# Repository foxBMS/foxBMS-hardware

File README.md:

# foxBMS

foxBMS is a free, open and flexible development environment to design battery
management systems. It is the first modular open source BMS development
platform.

## foxBMS Project Setup
The foxBMS project consists of several repositories.

The foxConda-installer repository contains the installer for the foxConda
environment. This environment provides all the tools necessary to generate the
documentation, compile the code for the MCUs and flash the generated binaries on
the MCUs (e.g., Python, git, GCC).

The starting point to get foxBMS is the foxBMS-setup
repository (https://github.com/foxBMS/foxBMS-setup), which contains
the general setup files for the foxBMS project. It includes a setup script
(bootstrap.py) which clones all the other needed repositories. The needed
documentation will be generated automatically after these repositories have been
cloned. The generated documentation is found in the directory ./build.
After the bootstrap step, the top project directory (foxBMS-setup) structure
looks like this:

 - foxBMS-setup <dir>
  - .git <dir> *
  - build <dir>
  - foxBMS-documentation <dir>
  - foxBMS-hardware <dir>
  - foxBMS-primary <dir>
  - foxBMS-secondary <dir>
  - foxBMS-tools <dir>
  - FreeRTOS <dir>
  - hal <dir>
  - .gitignore <file> *
  - bootstrap.py <file>
  - build.py <file>
  - CHANGELOG.md <file>
  - clean.py <file>
  - LICENSE.md <file>
  - README.md <file>
  - wscript <file>

* Directories and files with starting full stop are hidden in Windows in default
configuration.

There is a help available by running "python bootstrap.py -h".

## foxBMS Repositories

The foxConda-installer and foxBMS-setup repositories have already been described.

foxBMS is made out of two Microcontroller Units (MCU), named primary and
secondary. The C code for the primary MCU is found in the repository
foxBMS-primary (https://github.com/foxBMS/foxBMS-primary). The C code for the
secondary MCU is found in the repository foxBMS-secondary
(https://github.com/foxBMS/foxBMS-secondary). The Doxygen documentation is
generated from these sources into ./build/primary/doxygen/html and
./build/secondary/doxygen/html respectively. The main file is in both cases
index.html.

The layout and schematic files for the foxBMS hardware are found in the
foxBMS-hardware repository (https://github.com/foxBMS/foxBMS-hardware).

The Hardware Abstraction Layer (hal) for foxBMS is found in the hal-repository
(https://github.com/foxBMS/hal.) The real time operating system (FreeRTOS) for
foxBMS is found in the FreeRTOS-repository (https://github.com/foxBMS/FreeRTOS.)

The tools needed for foxBMS are in the foxBMS-tools-repository
(https://github.com/foxBMS/foxBMS-tools.)

The general documentation files for the foxBMS project are found in the
foxBMS-documentation repository
(https://github.com/foxBMS/foxBMS-documentation). The sphinx documentation is
found in foxBMS-documentation/doc/sphinx while the Doxygen documentation
configuration is found in foxBMS-documentation/doc/doxygen. The Doxygen
documentation itself is found in the software sources of the primary and
secondary microcontroller. The general documentation, rendered from the sphinx
sources is found in ./build/sphinx/foxBMS-documentation/doc/sphinx/html. The
main file is index.html

A generated version of the Sphinx documentation can be found at
http://foxbms.readthedocs.io/. It explains the structure of the
foxBMS hardware, how to install the foxConda environment and how to use foxConda
to compile and flash the sources.

## Building the Sources
For building the software, open a shell and type "python build.py -h". All
available build options will be displayed. The top build directory is ./build.

## Cleaning the ./build-Directory
For cleaning instructions open a shell and type "python clean.py -h". All
available cleaning options will be displayed.

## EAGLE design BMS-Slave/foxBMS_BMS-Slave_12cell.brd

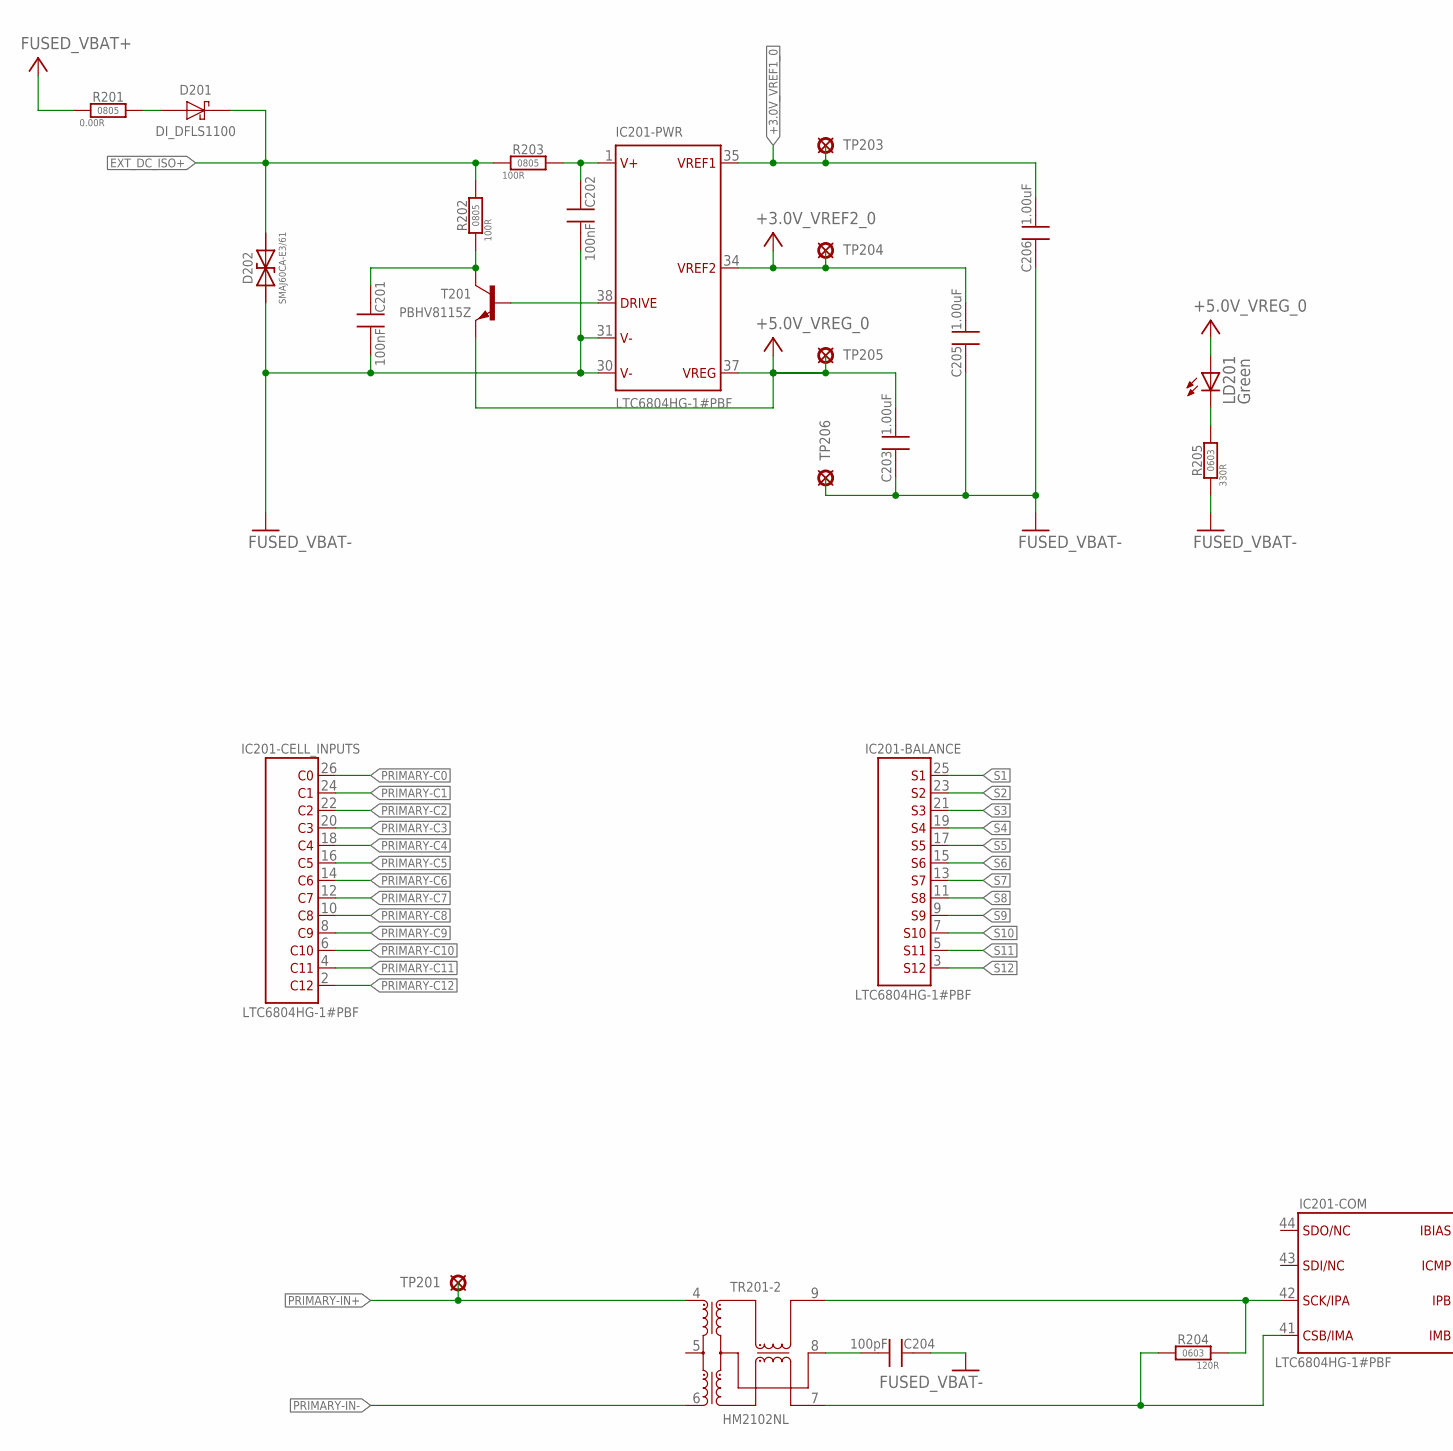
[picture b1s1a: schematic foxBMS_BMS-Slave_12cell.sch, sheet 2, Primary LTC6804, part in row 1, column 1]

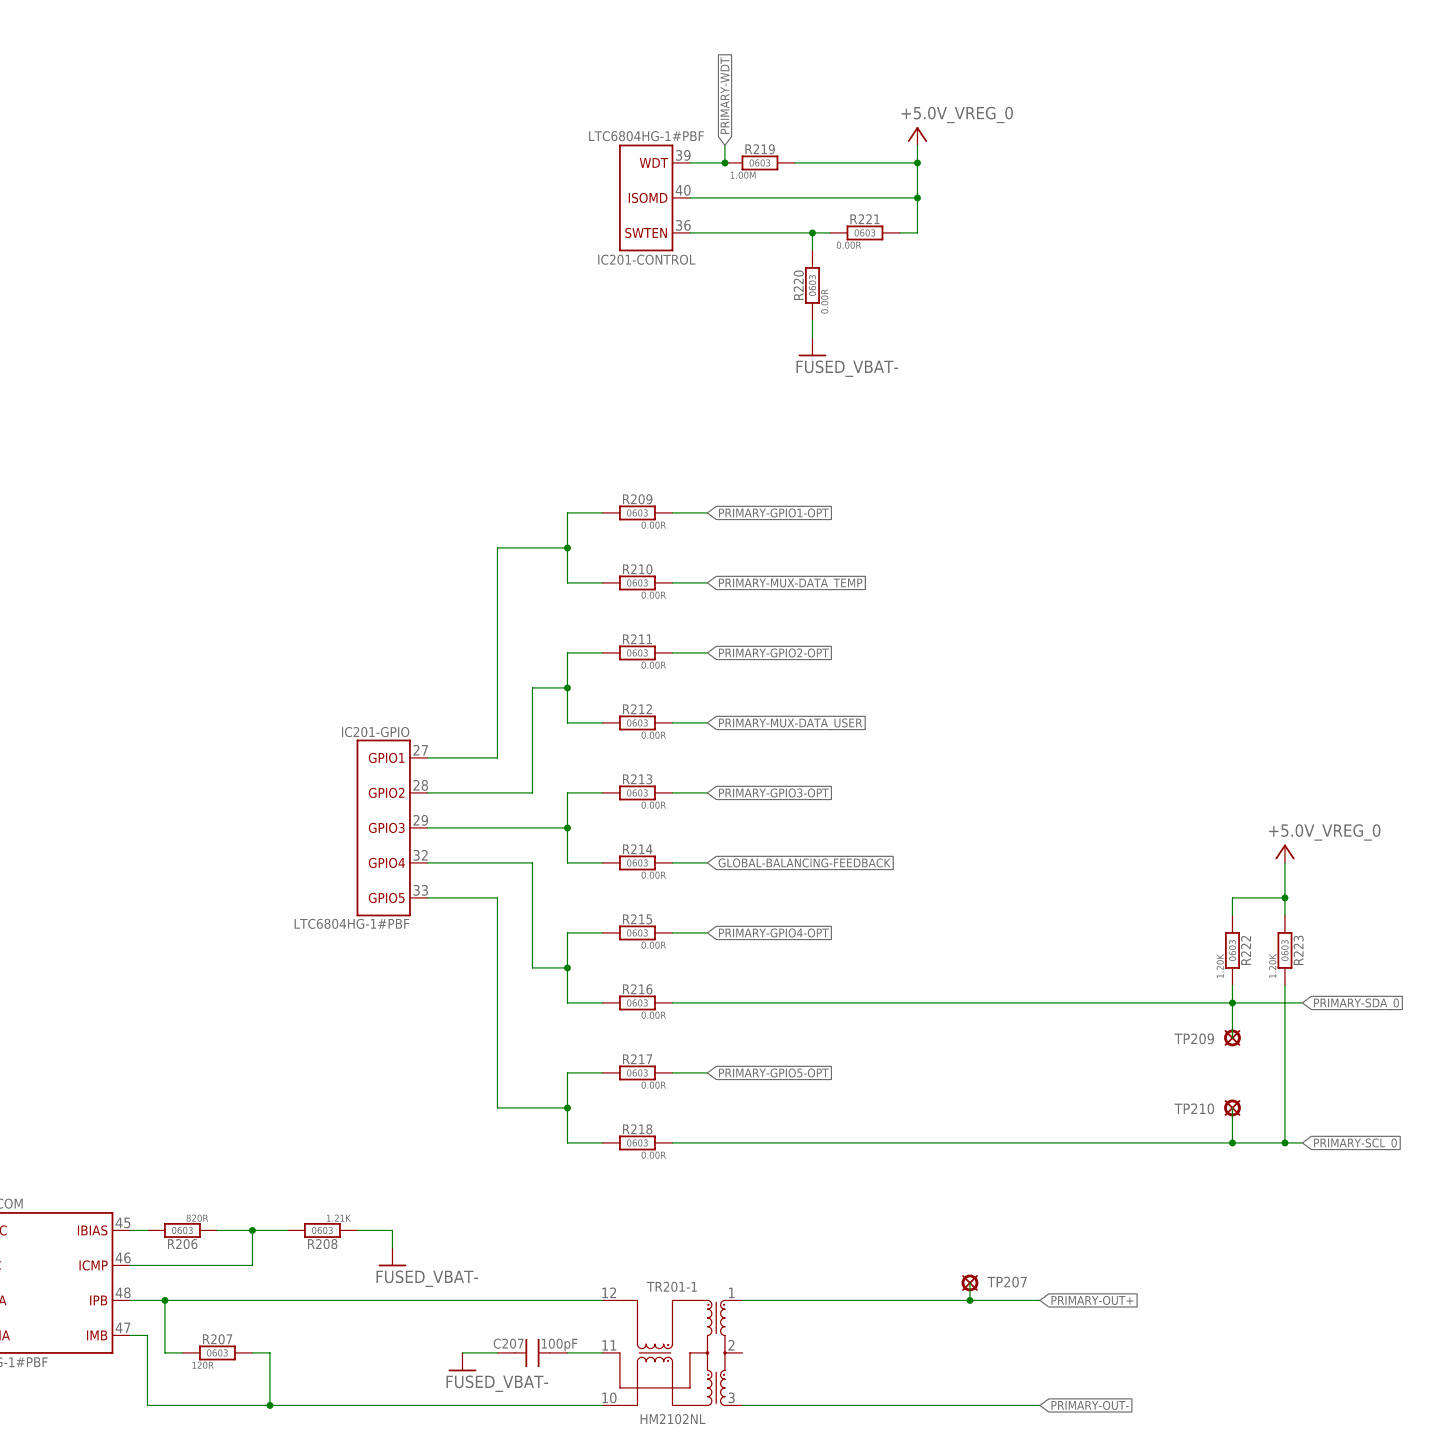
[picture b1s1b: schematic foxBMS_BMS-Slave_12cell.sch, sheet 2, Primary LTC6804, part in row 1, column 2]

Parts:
C201, C202: 100nF, 10%, 100V; C_SMD_0805_(2012)_R_MULTICOMP_REV01
C203, C205, C206: 1uF, 20%, 16V; C_SMD_0603_(1608)_R_KEMET_REV01
C204, C207: 100pF, 15%, 25V; C_SMD_0603_(1608)_R_KEMET_REV01
D201: DI_DFLS1100; POWER_DI_123
D202: SMAJ60CA_VISHAY; D_SMD_SMA_(DO-214AC)_(BIDIR)_R_VISHAY_REV01
IC201: 0_LES_BATTERIE-MANAGEMENT.SMD_LTC6804HG-1; 0_LES_BATTERIE-MANAGEMENT.SMD_IC_SMD_SSOP-48_(G48)_R_LINEAR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
LD201: Green; CHIP-LED0603
R201: 0,00R_0805_R_VISHAY_REV_01; R_SMD_0805_R_VISHAY_REV01
R202, R203: 100R, 1%, 1/10W; R_SMD_0805_R_VISHAY_REV01
R204, R207: 120R, 1%, 1/10W; R_SMD_0603_R_VISHAY_REV01
R205: 330R, 1%, 1/10W; R_SMD_0603_R_VISHAY_REV01
R206: 820R, 1%, 1/10W; R_SMD_0603_R_VISHAY_REV01
R208: 1.21k, 1%, 1/10W; R_SMD_0603_R_VISHAY_REV01
R209, R211, R213, R215, R217, R221: OPT; R_SMD_0603_R_VISHAY_REV01
R210, R212, R214, R216, R218, R220: 0R; R_SMD_0603_R_VISHAY_REV01
R219: 1M, 10%, 1/10W; R_SMD_0603_R_VISHAY_REV01
R222, R223: 1.2k, 10%, 1/10W; R_SMD_0603_R_VISHAY_REV01
T201: PBHV8115Z; D_SMD_SOT223_(SC-73)_R_NXP_REV01
TP201, TP203, TP204, TP205, TP206, TP207, TP209, TP210: CUSTOM_PAD_PAD_2.0X1.5MM; CUSTOM_PAD_PAD2.0X1.5MM
TR201: HM2102NL

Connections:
+3.0V_VREF1_0: C206.2, IC201.35 (VREF1), TP203.P$1
+3.0V_VREF2_0: C205.2, IC201.34 (VREF2), TP204.P$1; also elsewhere on the board
+5.0V_VREG_0: C203.2, IC201.37 (VREG), IC201.40 (ISOMD), LD201.A, R219.2, R221.2, R222.2, R223.2, T201.3 (E), TP205.P$1; also elsewhere on the board
EXT_DC_ISO+: D201.K (C), D202.C (K2), R202.2, R203.1; also elsewhere on the board
FUSED_VBAT+: R201.1; also elsewhere on the board
FUSED_VBAT-: C201.P$2, C202.P$2, C203.1, C204.1, C205.1, C206.1, C207.1, D202.A (K1), IC201.30 (V-1), IC201.31 (V-2), R205.1, R208.1, R220.1, TP206.P$1; also elsewhere on the board
GLOBAL-BALANCING-FEEDBACK: R214.1; also elsewhere on the board
unnamed: C207.2, TR201.11 (CMT)
unnamed: C201.P$1, R202.1, T201.2 (C), T201.4 (C)
unnamed: C204.2, TR201.8 (CMT)
unnamed: IC201.38 (DRIVE), T201.1 (B)
unnamed: IC201.45 (IBIAS), R206.2
unnamed: C202.P$1, IC201.1 (V+), R203.2
unnamed: LD201.C, R205.2
unnamed: D201.A, R201.2
PRIMARY-C0: IC201.26 (C0); also elsewhere on the board
PRIMARY-C1: IC201.24 (C1); also elsewhere on the board
PRIMARY-C2: IC201.22 (C2); also elsewhere on the board
PRIMARY-C3: IC201.20 (C3); also elsewhere on the board
PRIMARY-C4: IC201.18 (C4); also elsewhere on the board
PRIMARY-C5: IC201.16 (C5); also elsewhere on the board
PRIMARY-C6: IC201.14 (C6); also elsewhere on the board
PRIMARY-C7: IC201.12 (C7); also elsewhere on the board
PRIMARY-C8: IC201.10 (C8); also elsewhere on the board
PRIMARY-C9: IC201.8 (C9); also elsewhere on the board
PRIMARY-C10: IC201.6 (C10); also elsewhere on the board
PRIMARY-C11: IC201.4 (C11); also elsewhere on the board
PRIMARY-C12: IC201.2 (C12); also elsewhere on the board
PRIMARY-GPIO0: IC201.27 (GPIO1), R209.2, R210.2
PRIMARY-GPIO1: IC201.28 (GPIO2), R211.2, R212.2
PRIMARY-GPIO1-OPT: R209.1; also elsewhere on the board
PRIMARY-GPIO2-OPT: R211.1; also elsewhere on the board
PRIMARY-GPIO3: IC201.32 (GPIO4), R215.2, R216.2
PRIMARY-GPIO3-OPT: R213.1; also elsewhere on the board
PRIMARY-GPIO4: IC201.33 (GPIO5), R217.2, R218.2
PRIMARY-GPIO4-OPT: R215.1; also elsewhere on the board
PRIMARY-GPIO5: IC201.29 (GPIO3), R213.2, R214.2
PRIMARY-GPIO5-OPT: R217.1; also elsewhere on the board
PRIMARY-ICMP: IC201.46 (ICMP), R206.1, R208.2
PRIMARY-IN+: TP201.P$1, TR201.4 (D+); also elsewhere on the board
PRIMARY-IN-: TR201.6 (D-); also elsewhere on the board
PRIMARY-IN_N1: IC201.41 (CSB/IMA), R204.2, TR201.7 (X-)
PRIMARY-IN_P1: IC201.42 (SCK/IPA), R204.1, TR201.9 (X+)
PRIMARY-MUX-DATA_TEMP: R210.1; also elsewhere on the board
PRIMARY-MUX-DATA_USER: R212.1; also elsewhere on the board
PRIMARY-OUT+: TP207.P$1, TR201.1 (D+); also elsewhere on the board
PRIMARY-OUT-: TR201.3 (D-); also elsewhere on the board
PRIMARY-OUT_N1: IC201.47 (IMB), R207.2, TR201.10 (X-)
PRIMARY-OUT_P1: IC201.48 (IPB), R207.1, TR201.12 (X+)
PRIMARY-SCL_0: R218.1, R223.1, TP210.P$1; also elsewhere on the board
PRIMARY-SDA_0: R216.1, R222.1, TP209.P$1; also elsewhere on the board
PRIMARY-SWTEN: IC201.36 (SWTEN), R220.2, R221.1
PRIMARY-WDT: IC201.39 (WDT), R219.1; also elsewhere on the board
S1: IC201.25 (S1); also elsewhere on the board
S2: IC201.23 (S2); also elsewhere on the board
S3: IC201.21 (S3); also elsewhere on the board
S4: IC201.19 (S4); also elsewhere on the board
S5: IC201.17 (S5); also elsewhere on the board
S6: IC201.15 (S6); also elsewhere on the board
S7: IC201.13 (S7); also elsewhere on the board
S8: IC201.11 (S8); also elsewhere on the board
S9: IC201.9 (S9); also elsewhere on the board
S10: IC201.7 (S10); also elsewhere on the board
S11: IC201.5 (S11); also elsewhere on the board
S12: IC201.3 (S12); also elsewhere on the board

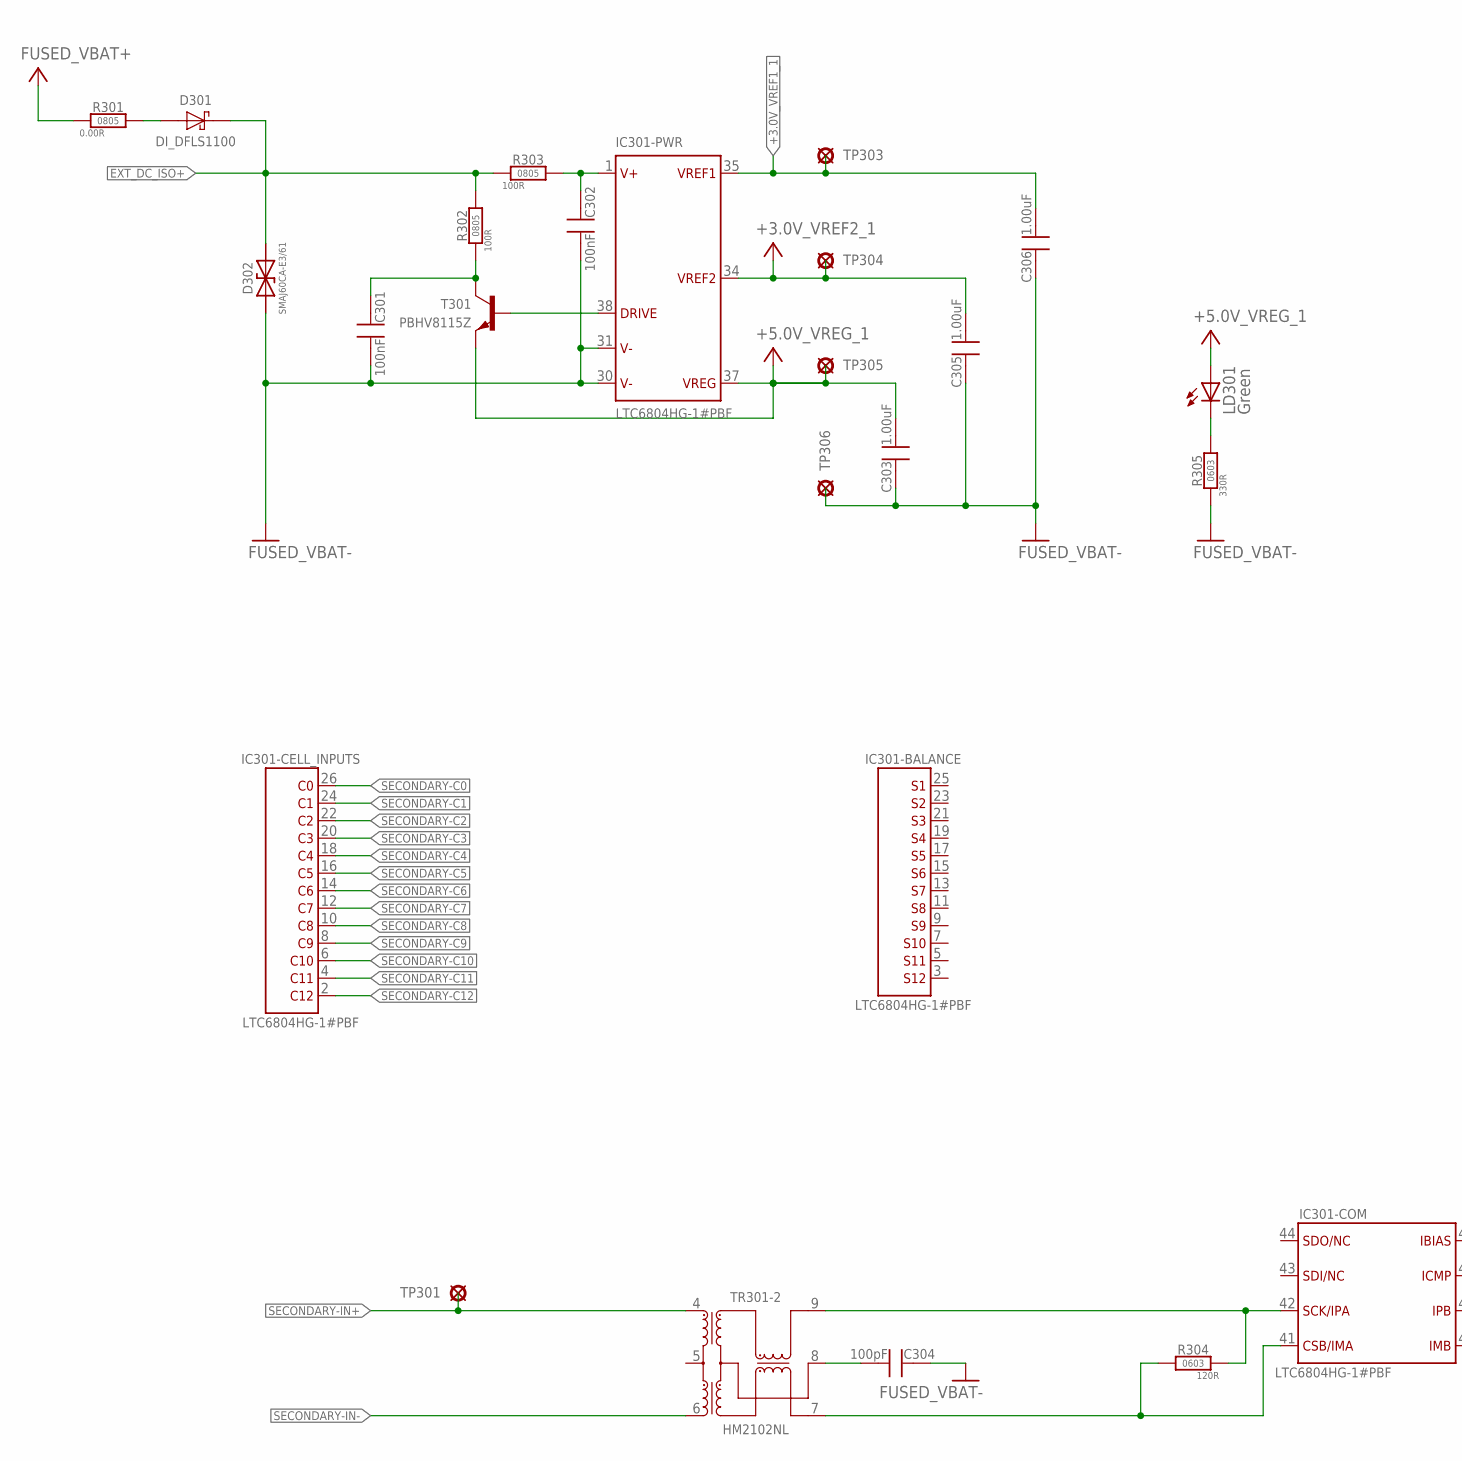
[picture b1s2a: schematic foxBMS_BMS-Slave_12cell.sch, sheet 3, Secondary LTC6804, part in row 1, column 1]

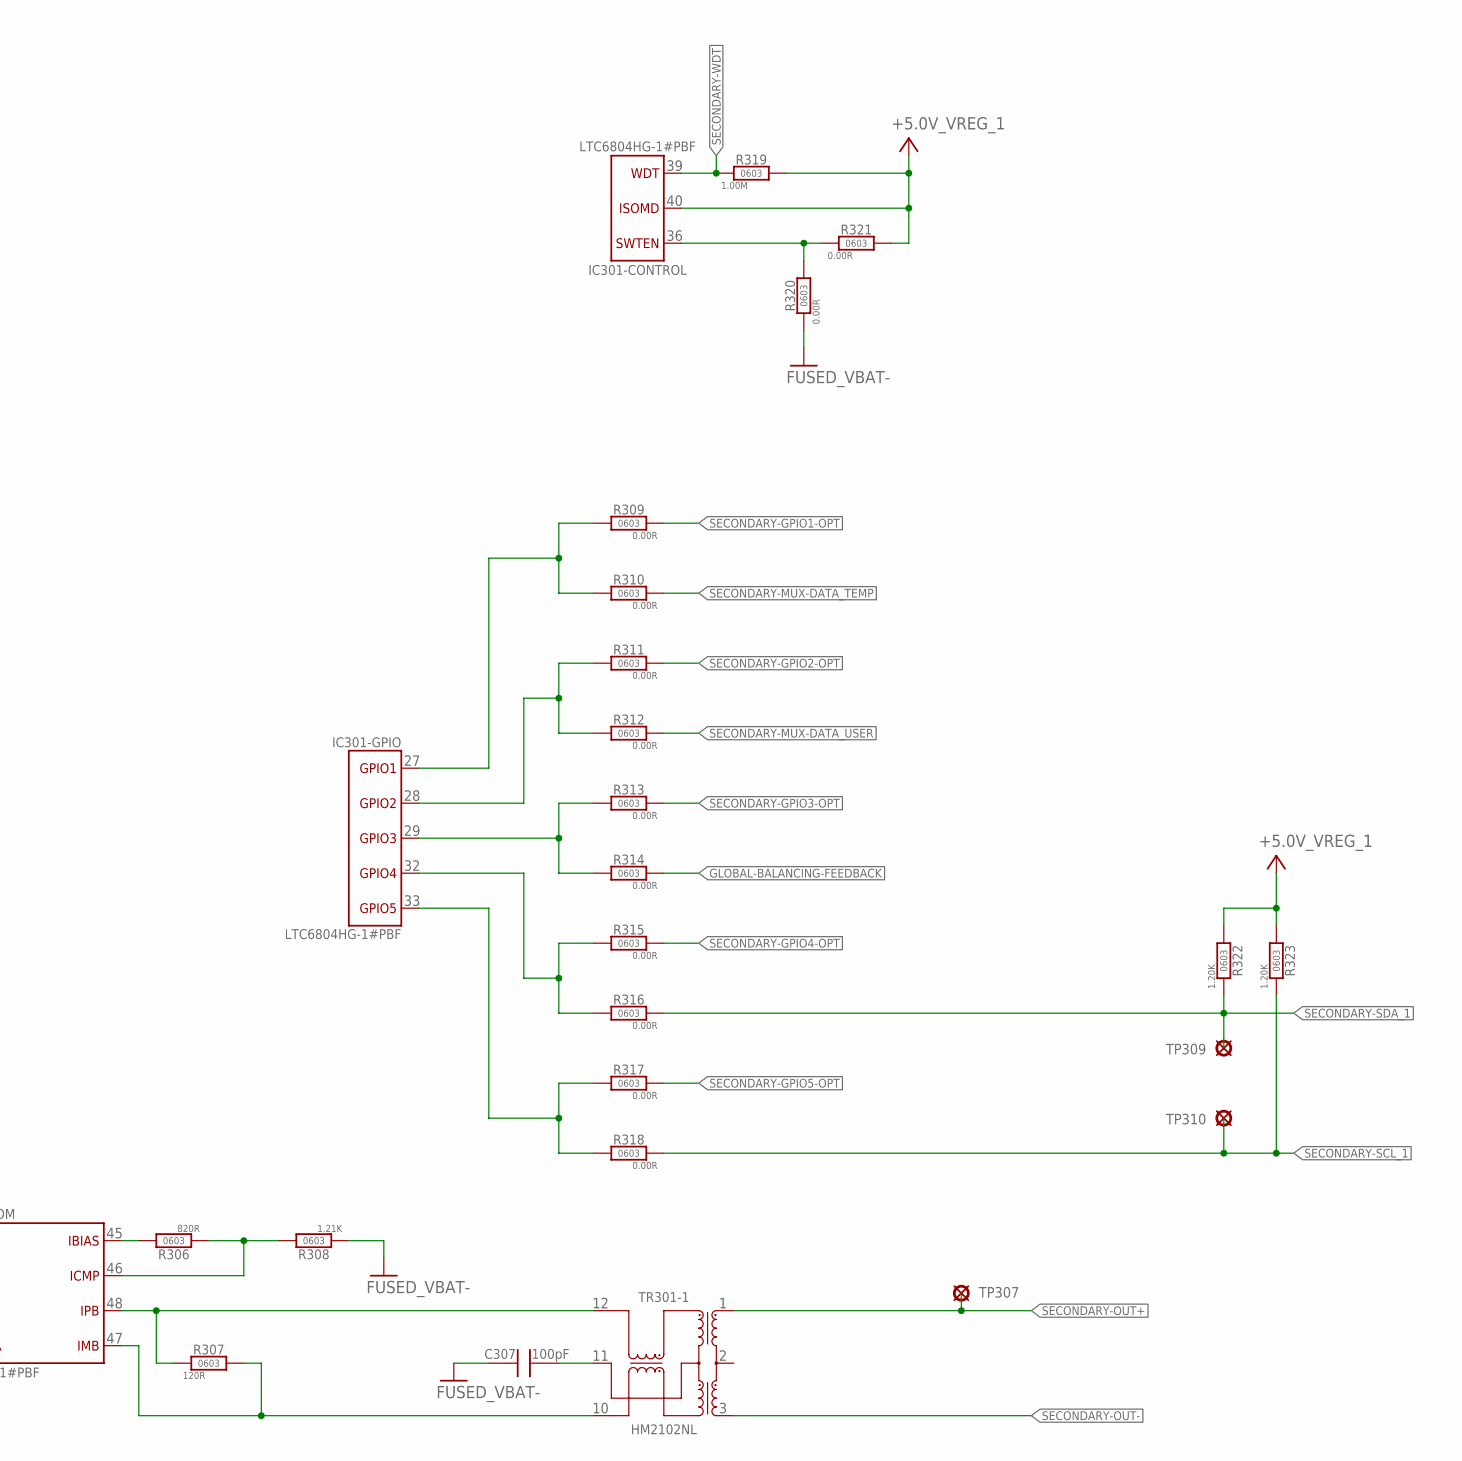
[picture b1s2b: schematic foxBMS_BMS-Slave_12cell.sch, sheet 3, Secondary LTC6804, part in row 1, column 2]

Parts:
C301, C302: 100nF, 10%, 100V; C_SMD_0805_(2012)_R_MULTICOMP_REV01
C303, C305, C306: 1uF, 20%, 16V; C_SMD_0603_(1608)_R_KEMET_REV01
C304, C307: 100pF, 15%, 25V; C_SMD_0603_(1608)_R_KEMET_REV01
D301: DI_DFLS1100; POWER_DI_123
D302: SMAJ60CA_VISHAY; D_SMD_SMA_(DO-214AC)_(BIDIR)_R_VISHAY_REV01
IC301: 0_LES_BATTERIE-MANAGEMENT.SMD_LTC6804HG-1; 0_LES_BATTERIE-MANAGEMENT.SMD_IC_SMD_SSOP-48_(G48)_R_LINEAR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
LD301: Green; CHIP-LED0603
R301: 0,00R_0805_R_VISHAY_REV_01; R_SMD_0805_R_VISHAY_REV01
R302, R303: 100R, 1%, 1/10W; R_SMD_0805_R_VISHAY_REV01
R304, R307: 120R, 1%, 1/10W; R_SMD_0603_R_VISHAY_REV01
R305: 330R, 1%, 1/10W; R_SMD_0603_R_VISHAY_REV01
R306: 820R, 1%, 1/10W; R_SMD_0603_R_VISHAY_REV01
R308: 1.21k, 1%, 1/10W; R_SMD_0603_R_VISHAY_REV01
R309, R311, R313, R315, R317, R321: OPT; R_SMD_0603_R_VISHAY_REV01
R310, R312, R314, R316, R318, R320: 0R; R_SMD_0603_R_VISHAY_REV01
R319: 1M, 10%, 1/10W; R_SMD_0603_R_VISHAY_REV01
R322, R323: 1.2k, 10%, 1/10W; R_SMD_0603_R_VISHAY_REV01
T301: PBHV8115Z; D_SMD_SOT223_(SC-73)_R_NXP_REV01
TP301, TP303, TP304, TP305, TP306, TP307, TP309, TP310: CUSTOM_PAD_PAD_2.0X1.5MM; CUSTOM_PAD_PAD2.0X1.5MM
TR301: HM2102NL

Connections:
+3.0V_VREF1_1: C306.2, IC301.35 (VREF1), TP303.P$1
+3.0V_VREF2_1: C305.2, IC301.34 (VREF2), TP304.P$1; also elsewhere on the board
+5.0V_VREG_1: C303.2, IC301.37 (VREG), IC301.40 (ISOMD), LD301.A, R319.2, R321.2, R322.2, R323.2, T301.3 (E), TP305.P$1; also elsewhere on the board
EXT_DC_ISO+: D301.K (C), D302.C (K2), R302.2, R303.1; also elsewhere on the board
FUSED_VBAT+: R301.1; also elsewhere on the board
FUSED_VBAT-: C301.P$2, C302.P$2, C303.1, C304.1, C305.1, C306.1, C307.1, D302.A (K1), IC301.30 (V-1), IC301.31 (V-2), R305.1, R308.1, R320.1, TP306.P$1; also elsewhere on the board
GLOBAL-BALANCING-FEEDBACK: R314.1; also elsewhere on the board
unnamed: C307.2, TR301.11 (CMT)
unnamed: C304.2, TR301.8 (CMT)
unnamed: C302.P$1, IC301.1 (V+), R303.2
unnamed: C301.P$1, R302.1, T301.2 (C), T301.4 (C)
unnamed: IC301.38 (DRIVE), T301.1 (B)
unnamed: IC301.45 (IBIAS), R306.2
unnamed: LD301.C, R305.2
unnamed: IC301.32 (GPIO4), R315.2, R316.2
unnamed: D301.A, R301.2
PRIMARY-ICMP1: IC301.46 (ICMP), R306.1, R308.2
PRIMARY-SWTEN1: IC301.36 (SWTEN), R320.2, R321.1
SECONDARY-C0: IC301.26 (C0); also elsewhere on the board
SECONDARY-C1: IC301.24 (C1); also elsewhere on the board
SECONDARY-C2: IC301.22 (C2); also elsewhere on the board
SECONDARY-C3: IC301.20 (C3); also elsewhere on the board
SECONDARY-C4: IC301.18 (C4); also elsewhere on the board
SECONDARY-C5: IC301.16 (C5); also elsewhere on the board
SECONDARY-C6: IC301.14 (C6); also elsewhere on the board
SECONDARY-C7: IC301.12 (C7); also elsewhere on the board
SECONDARY-C8: IC301.10 (C8); also elsewhere on the board
SECONDARY-C9: IC301.8 (C9); also elsewhere on the board
SECONDARY-C10: IC301.6 (C10); also elsewhere on the board
SECONDARY-C11: IC301.4 (C11); also elsewhere on the board
SECONDARY-C12: IC301.2 (C12); also elsewhere on the board
SECONDARY-GPIO0: IC301.27 (GPIO1), R309.2, R310.2
SECONDARY-GPIO1: IC301.28 (GPIO2), R311.2, R312.2
SECONDARY-GPIO1-OPT: R309.1; also elsewhere on the board
SECONDARY-GPIO2-OPT: R311.1; also elsewhere on the board
SECONDARY-GPIO3-OPT: R313.1; also elsewhere on the board
SECONDARY-GPIO4: IC301.33 (GPIO5), R317.2, R318.2
SECONDARY-GPIO4-OPT: R315.1; also elsewhere on the board
SECONDARY-GPIO5: IC301.29 (GPIO3), R313.2, R314.2
SECONDARY-GPIO5-OPT: R317.1; also elsewhere on the board
SECONDARY-IN+: TP301.P$1, TR301.4 (D+); also elsewhere on the board
SECONDARY-IN-: TR301.6 (D-); also elsewhere on the board
SECONDARY-IN_N1: IC301.41 (CSB/IMA), R304.2, TR301.7 (X-)
SECONDARY-IN_P1: IC301.42 (SCK/IPA), R304.1, TR301.9 (X+)
SECONDARY-MUX-DATA_TEMP: R310.1; also elsewhere on the board
SECONDARY-MUX-DATA_USER: R312.1; also elsewhere on the board
SECONDARY-OUT+: TP307.P$1, TR301.1 (D+); also elsewhere on the board
SECONDARY-OUT-: TR301.3 (D-); also elsewhere on the board
SECONDARY-OUT_N1: IC301.47 (IMB), R307.2, TR301.10 (X-)
SECONDARY-OUT_P1: IC301.48 (IPB), R307.1, TR301.12 (X+)
SECONDARY-SCL_1: R318.1, R323.1, TP310.P$1; also elsewhere on the board
SECONDARY-SDA_1: R316.1, R322.1, TP309.P$1; also elsewhere on the board
SECONDARY-WDT: IC301.39 (WDT), R319.1; also elsewhere on the board

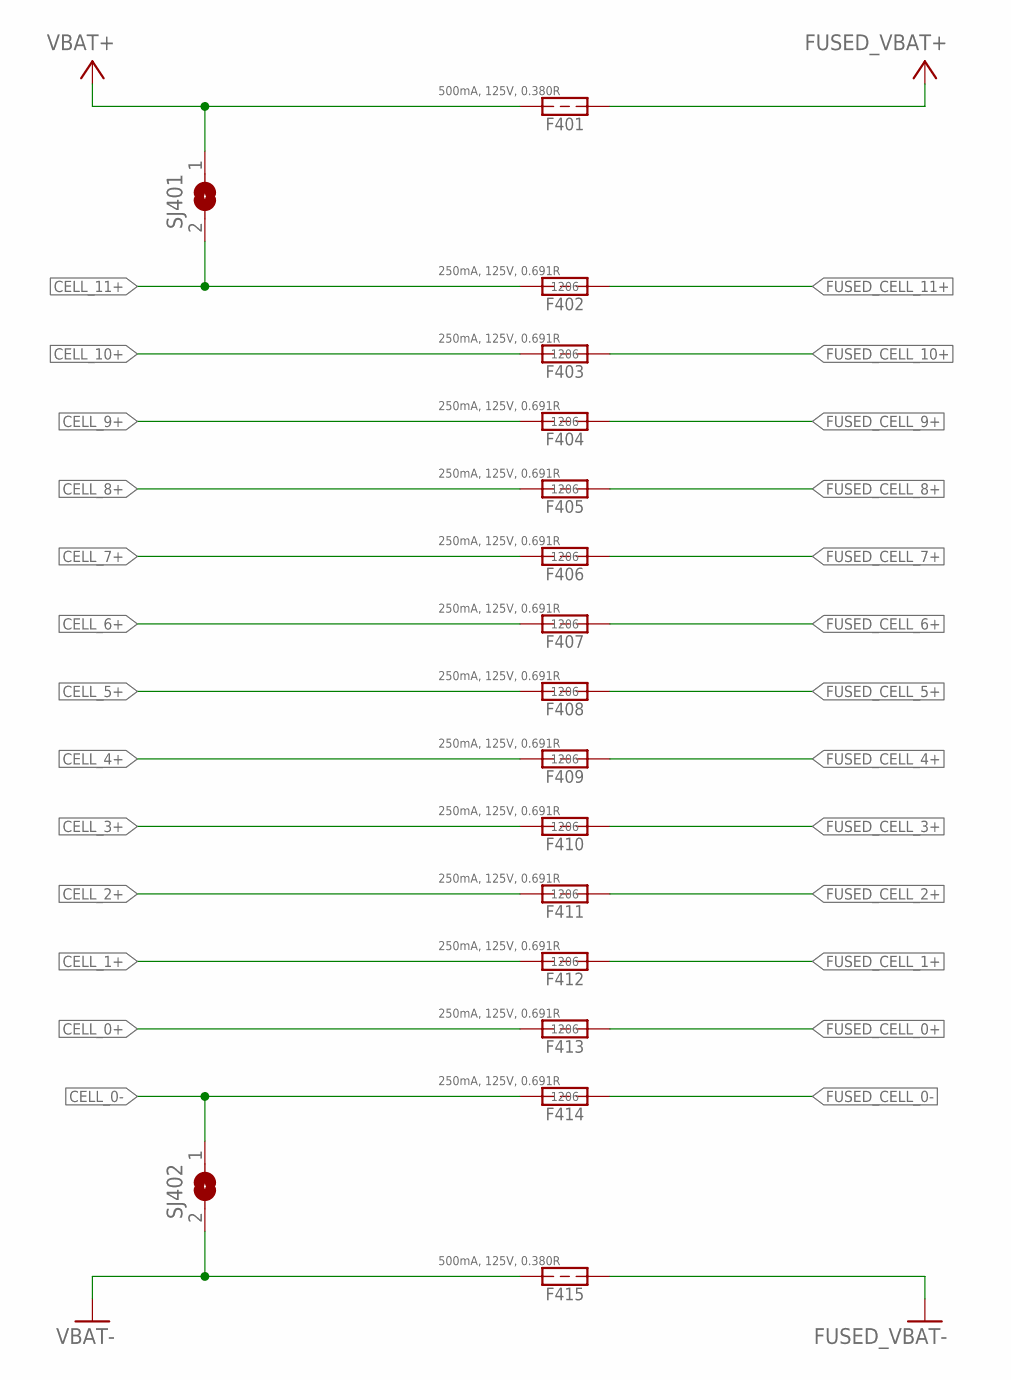
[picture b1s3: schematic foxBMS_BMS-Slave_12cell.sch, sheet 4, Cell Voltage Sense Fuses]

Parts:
F401, F415: 0.5A, 63V, 0.25R; 448_SERIES_LITTELFUSE
F402, F403, F404, F405, F406, F407, F408, F409, F410, F411, F412, F413, F414: FUSE: 0.250A, 32V, 0.57R; R_SMD_CHIP_1206_R_LITTLEFUSE_REV_01
SJ401, SJ402: SJ

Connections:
CELL_0+: F413.P$1; also elsewhere on the board
CELL_0-: F414.P$1, SJ402.1; also elsewhere on the board
CELL_1+: F412.P$1; also elsewhere on the board
CELL_2+: F411.P$1; also elsewhere on the board
CELL_3+: F410.P$1; also elsewhere on the board
CELL_4+: F409.P$1; also elsewhere on the board
CELL_5+: F408.P$1; also elsewhere on the board
CELL_6+: F407.P$1; also elsewhere on the board
CELL_7+: F406.P$1; also elsewhere on the board
CELL_8+: F405.P$1; also elsewhere on the board
CELL_9+: F404.P$1; also elsewhere on the board
CELL_10+: F403.P$1; also elsewhere on the board
CELL_11+: F402.P$1, SJ401.2; also elsewhere on the board
FUSED_CELL_0+: F413.P$2; also elsewhere on the board
FUSED_CELL_0-: F414.P$2; also elsewhere on the board
FUSED_CELL_1+: F412.P$2; also elsewhere on the board
FUSED_CELL_2+: F411.P$2; also elsewhere on the board
FUSED_CELL_3+: F410.P$2; also elsewhere on the board
FUSED_CELL_4+: F409.P$2; also elsewhere on the board
FUSED_CELL_5+: F408.P$2; also elsewhere on the board
FUSED_CELL_6+: F407.P$2; also elsewhere on the board
FUSED_CELL_7+: F406.P$2; also elsewhere on the board
FUSED_CELL_8+: F405.P$2; also elsewhere on the board
FUSED_CELL_9+: F404.P$2; also elsewhere on the board
FUSED_CELL_10+: F403.P$2; also elsewhere on the board
FUSED_CELL_11+: F402.P$2; also elsewhere on the board
FUSED_VBAT+: F401.P$2; also elsewhere on the board
FUSED_VBAT-: F415.P$2; also elsewhere on the board
VBAT+: F401.P$1, SJ401.1; also elsewhere on the board
VBAT-: F415.P$1, SJ402.2; also elsewhere on the board

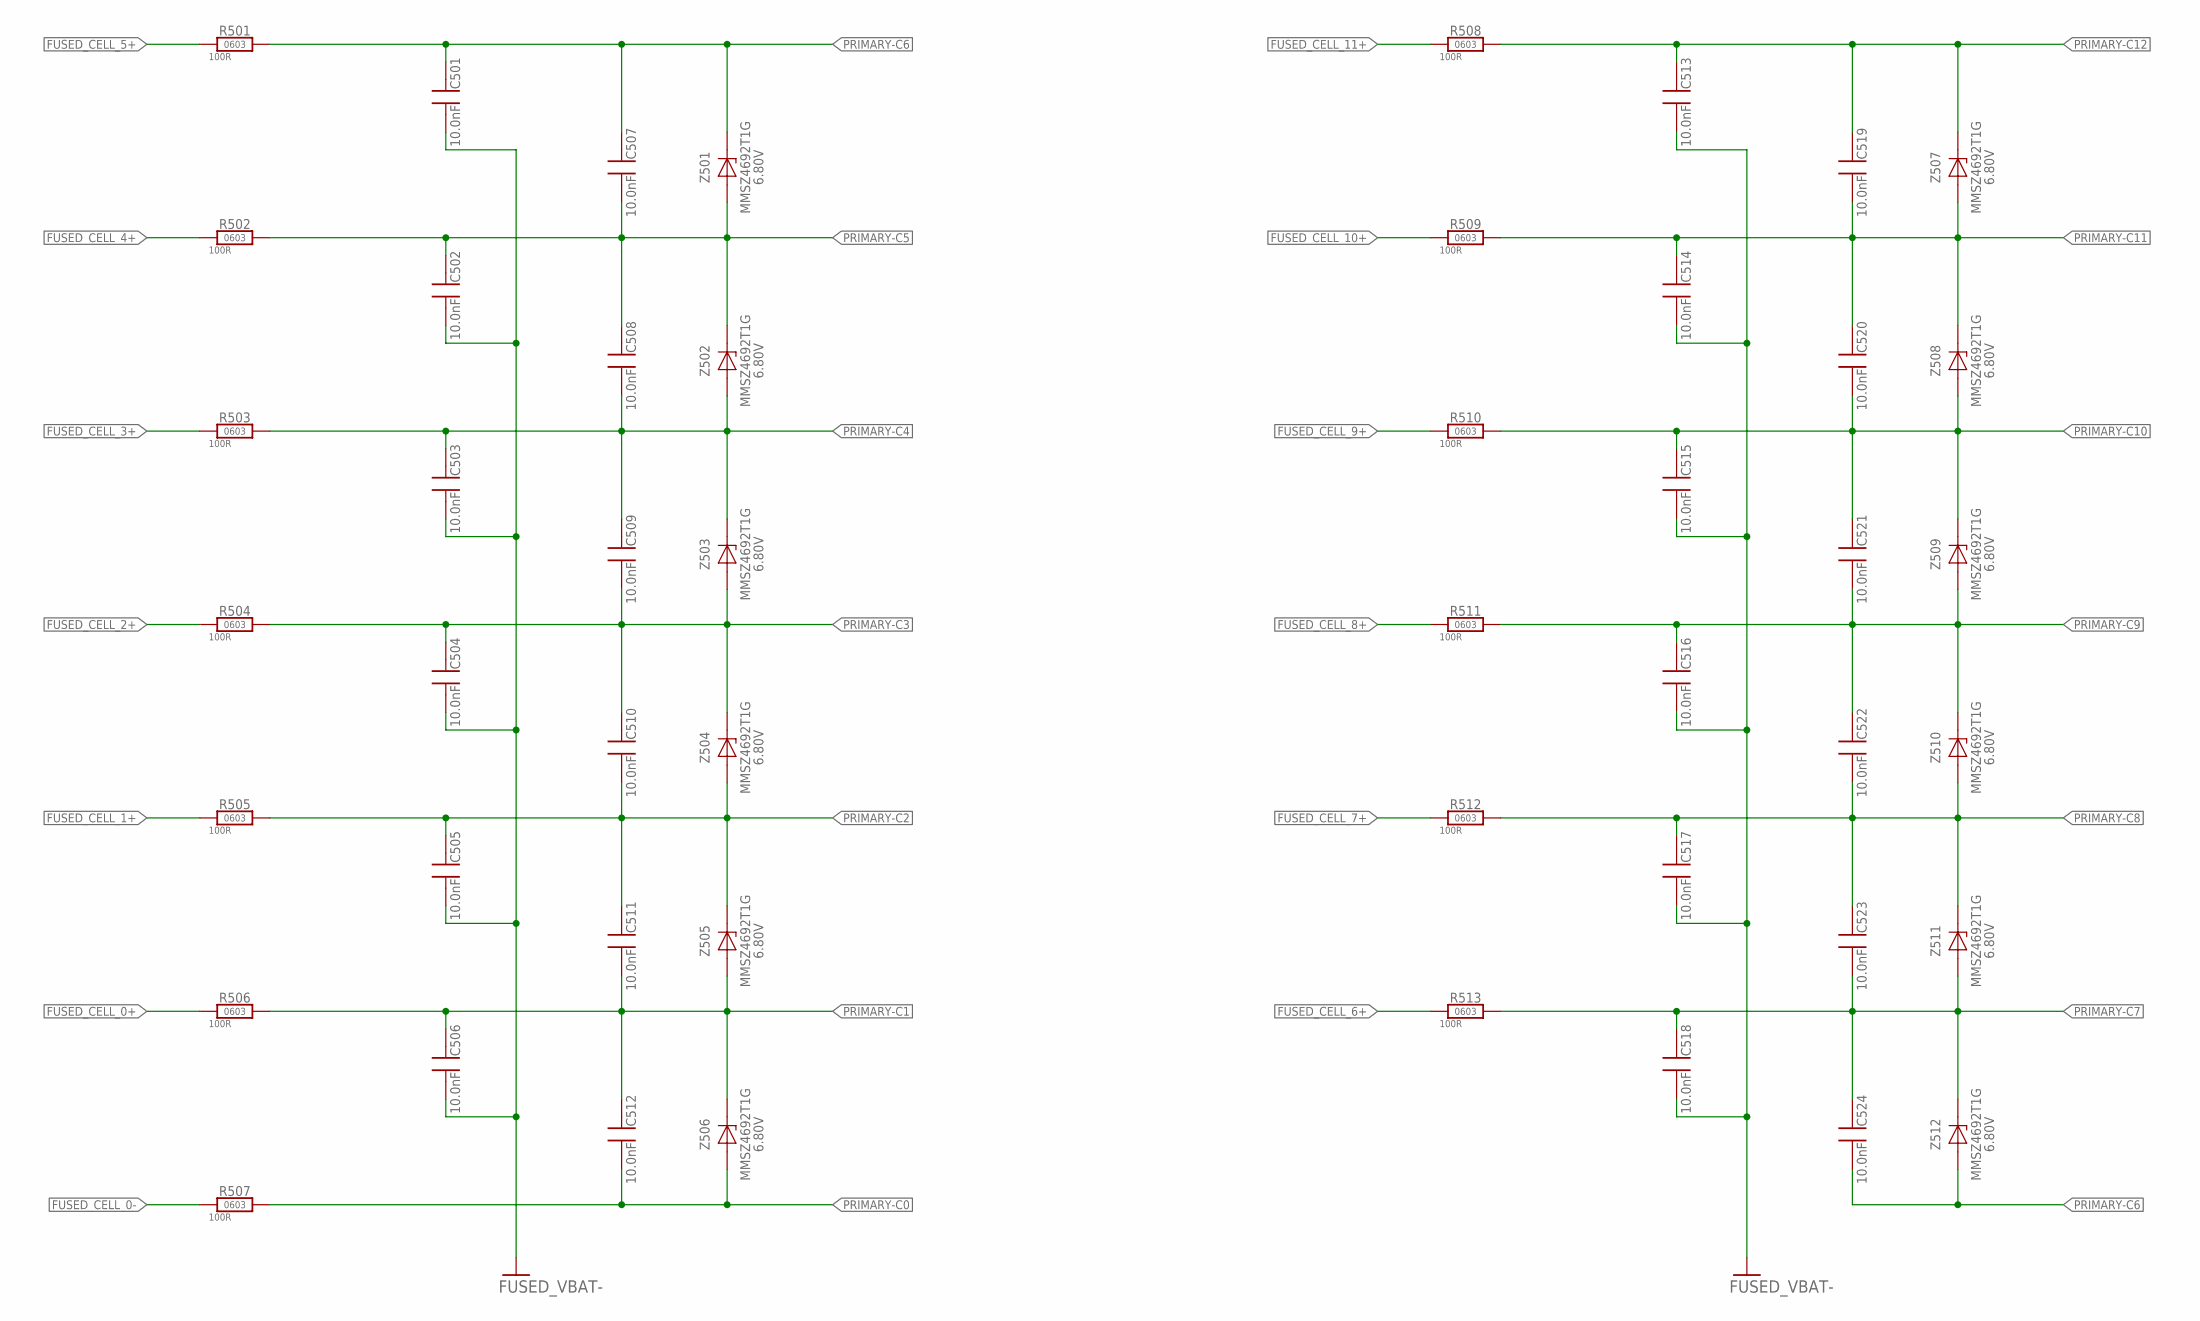
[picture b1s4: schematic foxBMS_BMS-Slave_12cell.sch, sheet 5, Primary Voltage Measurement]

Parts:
C501, C502, C503, C504, C505, C506, C507, C508, C509, C510, C511, C512, C513, C514, C515, C516, C517, C518, C519, C520, C521, C522, C523, C524: 10nF, 100V, 10%; C_SMD_0603_(1608)_R_KEMET_REV01
R501, R502, R503, R504, R505, R506, R507, R508, R509, R510, R511, R512, R513: 100R_0603_R_VISHAY_1%_TK100_REV_01; R_SMD_0603_R_VISHAY_REV01
Z501, Z502, Z503, Z504, Z505, Z506, Z507, Z508, Z509, Z510, Z511, Z512: 6.8V, 500mW; D_SMD_SOD-123_R_ON_REV01

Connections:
FUSED_CELL_0+: R506.1; also elsewhere on the board
FUSED_CELL_0-: R507.1; also elsewhere on the board
FUSED_CELL_1+: R505.1; also elsewhere on the board
FUSED_CELL_2+: R504.1; also elsewhere on the board
FUSED_CELL_3+: R503.1; also elsewhere on the board
FUSED_CELL_4+: R502.1; also elsewhere on the board
FUSED_CELL_5+: R501.1; also elsewhere on the board
FUSED_CELL_6+: R513.1; also elsewhere on the board
FUSED_CELL_7+: R512.1; also elsewhere on the board
FUSED_CELL_8+: R511.1; also elsewhere on the board
FUSED_CELL_9+: R510.1; also elsewhere on the board
FUSED_CELL_10+: R509.1; also elsewhere on the board
FUSED_CELL_11+: R508.1; also elsewhere on the board
FUSED_VBAT-: C501.2, C502.2, C503.2, C504.2, C505.2, C506.2, C513.2, C514.2, C515.2, C516.2, C517.2, C518.2; also elsewhere on the board
PRIMARY-C0: C512.2, R507.2, Z506.A; also elsewhere on the board
PRIMARY-C1: C506.1, C511.2, C512.1, R506.2, Z505.A, Z506.K (C); also elsewhere on the board
PRIMARY-C2: C505.1, C510.2, C511.1, R505.2, Z504.A, Z505.K (C); also elsewhere on the board
PRIMARY-C3: C504.1, C509.2, C510.1, R504.2, Z503.A, Z504.K (C); also elsewhere on the board
PRIMARY-C4: C503.1, C508.2, C509.1, R503.2, Z502.A, Z503.K (C); also elsewhere on the board
PRIMARY-C5: C502.1, C507.2, C508.1, R502.2, Z501.A, Z502.K (C); also elsewhere on the board
PRIMARY-C6: C501.1, C507.1, C524.2, R501.2, Z501.K (C), Z512.A; also elsewhere on the board
PRIMARY-C7: C518.1, C523.2, C524.1, R513.2, Z511.A, Z512.K (C); also elsewhere on the board
PRIMARY-C8: C517.1, C522.2, C523.1, R512.2, Z510.A, Z511.K (C); also elsewhere on the board
PRIMARY-C9: C516.1, C521.2, C522.1, R511.2, Z509.A, Z510.K (C); also elsewhere on the board
PRIMARY-C10: C515.1, C520.2, C521.1, R510.2, Z508.A, Z509.K (C); also elsewhere on the board
PRIMARY-C11: C514.1, C519.2, C520.1, R509.2, Z507.A, Z508.K (C); also elsewhere on the board
PRIMARY-C12: C513.1, C519.1, R508.2, Z507.K (C); also elsewhere on the board

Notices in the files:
BMS-Extension/foxBMS_BMS-Extension.brd:
Creative Commons
Attribution 4.0
parts and their libraries:
foxBMS_BMS-Master_V1.00_A: LICENSE: Creative Commons Attribution 4.0
